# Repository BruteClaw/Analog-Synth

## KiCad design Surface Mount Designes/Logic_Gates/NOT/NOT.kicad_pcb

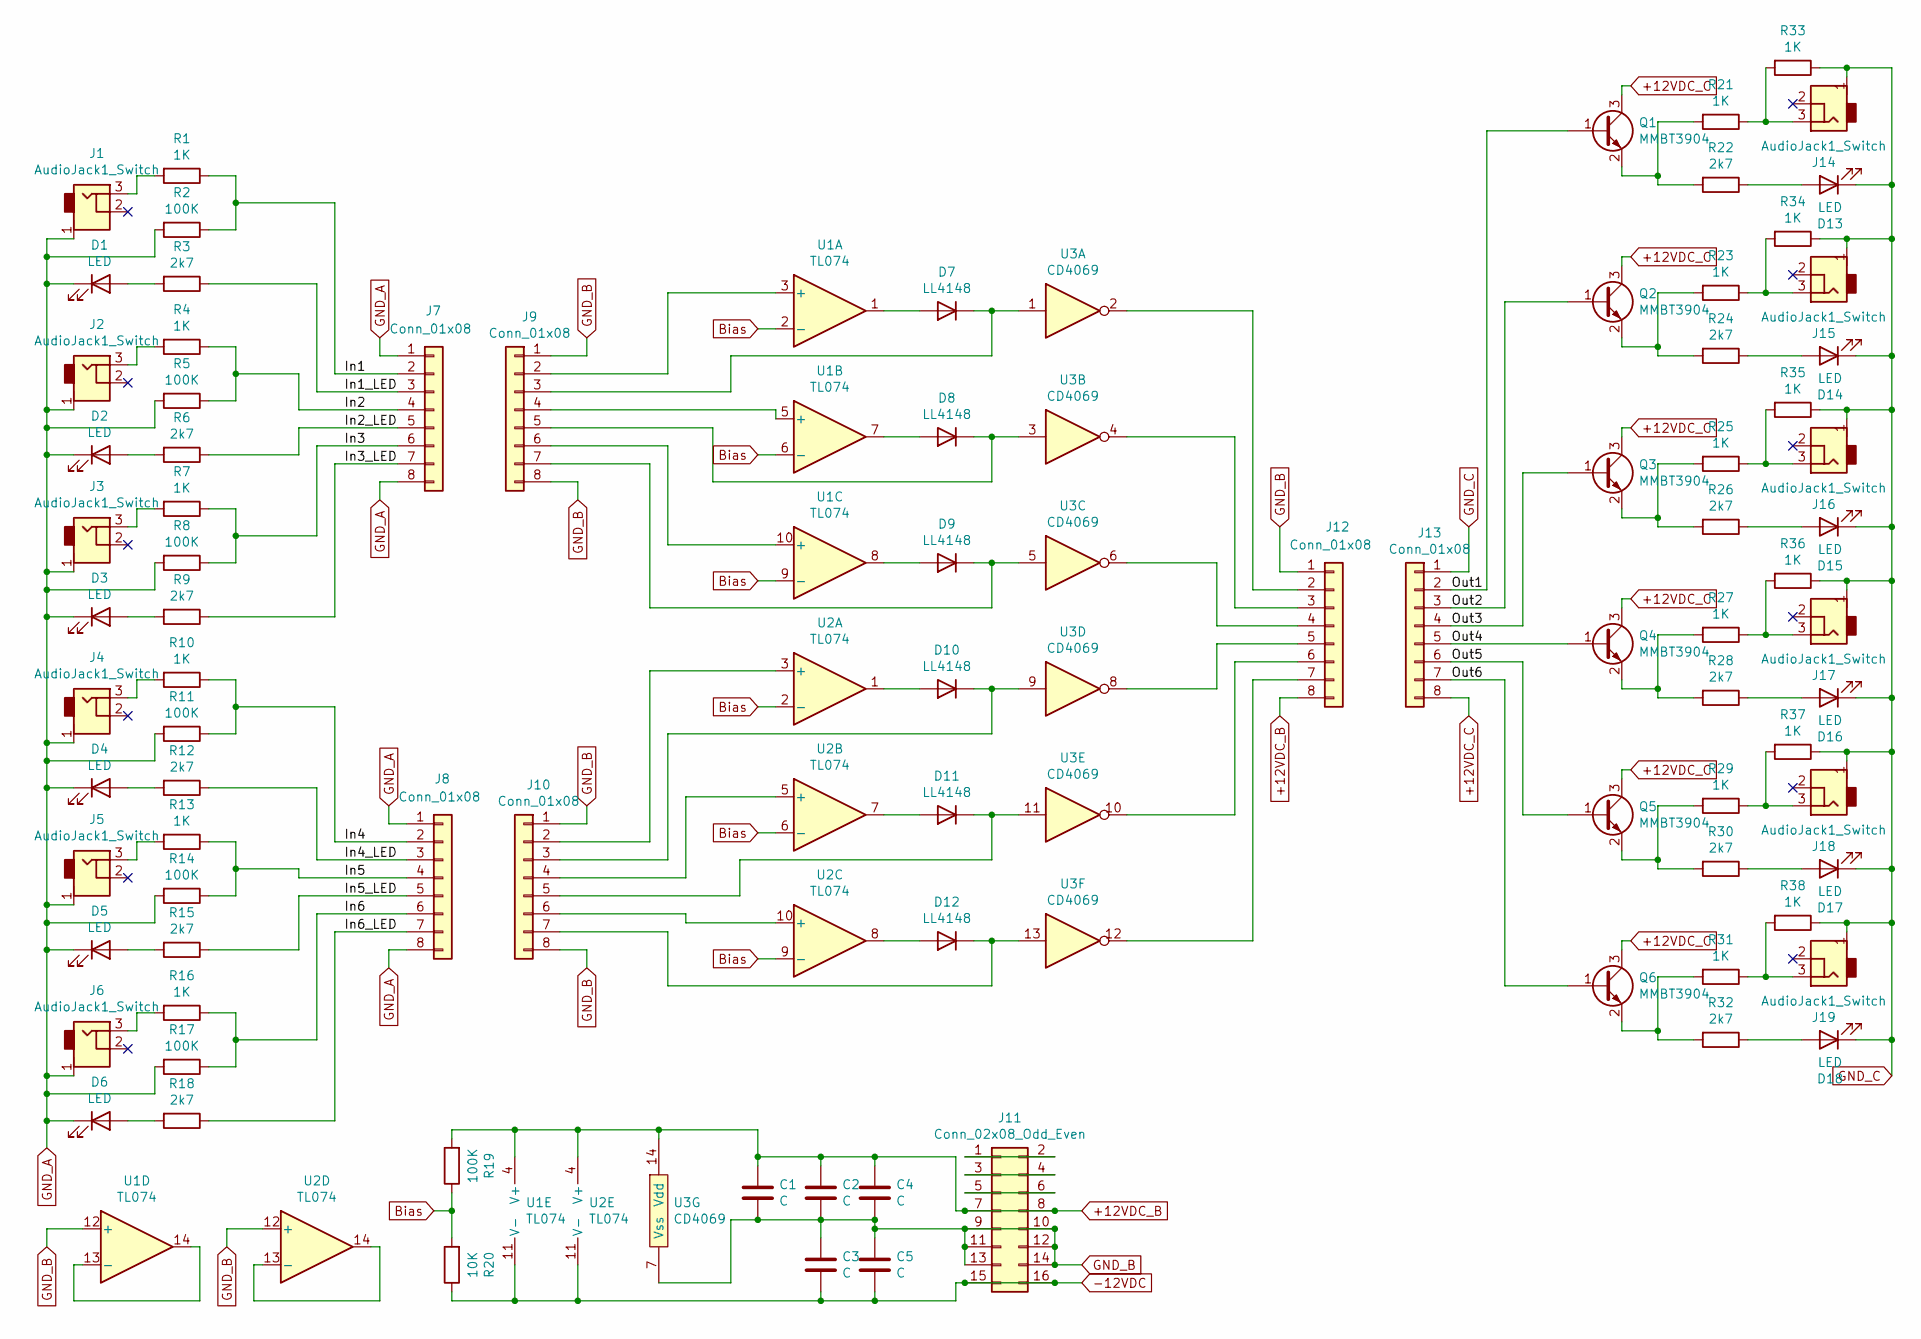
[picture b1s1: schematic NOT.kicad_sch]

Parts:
C1, C2, C3, C4, C5: C; C_1210_HandSoldering
D1, D2, D3, D4, D5, D6, D13, D14, D15, D16, D17, D18: LED; LED_Rectangular_W3.9mm_H1.9mm
D7, D8, D9, D10, D11, D12: LL4148; D_MiniMELF_Handsoldering
J1, J2, J3, J4, J5, J6, J14, J15, J16, J17, J18, J19: AudioJack1_Switch; Mono_Jack_3.5mm_Switch_Switchcraft_35RAPC2AH3
J7, J8, J9, J10, J12, J13: Conn_01x08; Pin_Header_Straight_1x08_Pitch2.54mm
J11: Conn_02x08_Odd_Even; Pin_Header_Straight_2x08_Pitch2.54mm
Q1, Q2, Q3, Q4, Q5, Q6: MMBT3904; SOT-23
R1, R4, R7, R10, R13, R16, R21, R23, R25, R27, R29, R31, R33, R34, R35, R36, R37, R38: 1K; R_1210_HandSoldering
R2, R5, R8, R11, R14, R17, R19: 100K; R_1210_HandSoldering
R3, R6, R9, R12, R15, R18, R22, R24, R26, R28, R30, R32: 2k7; R_1210_HandSoldering
R20: 10K; R_1210_HandSoldering
U1, U2: TL074; SOIC-14_3.9x8.7mm_Pitch1.27mm
U3: CD4069; SOIC-14_3.9x8.7mm_Pitch1.27mm

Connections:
+12VDC_B: C1.1, C2.1, C4.1, J11.7, J11.8, J12.8, R19.2, U1.4 (V+), U2.4 (V+), U3.14 (Vdd)
+12VDC_C: J13.8, Q1.3 (C), Q2.3 (C), Q3.3 (C), Q4.3 (C), Q5.3 (C), Q6.3 (C)
-12VDC: C3.2, C5.2, J11.15, J11.16, R20.1, U1.11 (V-), U2.11 (V-)
/In1: J7.2, R1.1, R2.1
/In1_LED: J7.3, R3.1
/In2: J7.4, R4.1, R5.1
/In2_LED: J7.5, R6.1
/In3: J7.6, R7.1, R8.1
/In3_LED: J7.7, R9.1
/In4: J8.2, R10.1, R11.1
/In4_LED: J8.3, R12.1
/In5: J8.4, R13.1, R14.1
/In5_LED: J8.5, R15.1
/In6: J8.6, R16.1, R17.1
/In6_LED: J8.7, R18.1
/Out1: J13.2, Q1.1 (B)
/Out2: J13.3, Q2.1 (B)
/Out3: J13.4, Q3.1 (B)
/Out4: J13.5, Q4.1 (B)
/Out5: J13.6, Q5.1 (B)
/Out6: J13.7, Q6.1 (B)
Bias: R19.1, R20.2, U1.2 (-), U1.6 (-), U1.9 (-), U2.2 (-), U2.6 (-), U2.9 (-)
GND_A: D1.1 (K), D2.1 (K), D3.1 (K), D4.1 (K), D5.1 (K), D6.1 (K), J1.1, J2.1, J3.1, J4.1, J5.1, J6.1, J7.1, J7.8, J8.1, J8.8, R2.2, R5.2, R8.2, R11.2, R14.2, R17.2
GND_B: C1.2, C2.2, C3.1, C4.2, C5.1, J9.1, J9.8, J10.1, J10.8, J11.9, J11.10, J11.11, J11.12, J11.13, J11.14, J12.1, U1.12 (+), U2.12 (+), U3.7 (Vss)
GND_C: D13.1 (K), D14.1 (K), D15.1 (K), D16.1 (K), D17.1 (K), D18.1 (K), J13.1, J14.1, J15.1, J16.1, J17.1, J18.1, J19.1, R33.1, R34.1, R35.1, R36.1, R37.1, R38.1
unnamed: D1.2 (A), R3.2
unnamed: D2.2 (A), R6.2
unnamed: D3.2 (A), R9.2
unnamed: D4.2 (A), R12.2
unnamed: D5.2 (A), R15.2
unnamed: D6.2 (A), R18.2
unnamed: D7.1 (K), J9.3, U3.1
unnamed: D7.2 (A), U1.1
unnamed: D8.1 (K), J9.5, U3.3
unnamed: D8.2 (A), U1.7
unnamed: D9.1 (K), J9.7, U3.5
unnamed: D9.2 (A), U1.8
unnamed: D10.1 (K), J10.3, U3.9
unnamed: D10.2 (A), U2.1
unnamed: D11.1 (K), J10.5, U3.11
unnamed: D11.2 (A), U2.7
unnamed: D12.1 (K), J10.7, U3.13
unnamed: D12.2 (A), U2.8
unnamed: D13.2 (A), R22.1
unnamed: D14.2 (A), R24.1
unnamed: D15.2 (A), R26.1
unnamed: D16.2 (A), R28.1
unnamed: D17.2 (A), R30.1
unnamed: D18.2 (A), R32.1
unnamed: J1.3, R1.2
unnamed: J2.3, R4.2
unnamed: J3.3, R7.2
unnamed: J4.3, R10.2
unnamed: J5.3, R13.2
unnamed: J6.3, R16.2
unnamed: J9.2, U1.3 (+)
unnamed: J9.4, U1.5 (+)
unnamed: J9.6, U1.10 (+)
unnamed: J10.2, U2.3 (+)
unnamed: J10.4, U2.5 (+)
unnamed: J10.6, U2.10 (+)
unnamed: J11.1, J11.2
unnamed: J11.3, J11.4
unnamed: J11.5, J11.6
unnamed: J12.2, U3.2
unnamed: J12.3, U3.4
unnamed: J12.4, U3.6
unnamed: J12.5, U3.8
unnamed: J12.6, U3.10
unnamed: J12.7, U3.12
unnamed: J14.3, R21.1, R33.2
unnamed: J15.3, R23.1, R34.2
unnamed: J16.3, R25.1, R35.2
unnamed: J17.3, R27.1, R36.2
unnamed: J18.3, R29.1, R37.2
unnamed: J19.3, R31.1, R38.2
unnamed: Q1.2 (E), R21.2, R22.2
unnamed: Q2.2 (E), R23.2, R24.2
unnamed: Q3.2 (E), R25.2, R26.2
unnamed: Q4.2 (E), R27.2, R28.2
unnamed: Q5.2 (E), R29.2, R30.2
unnamed: Q6.2 (E), R31.2, R32.2
unnamed: U1.13 (-), U1.14
unnamed: U2.13 (-), U2.14

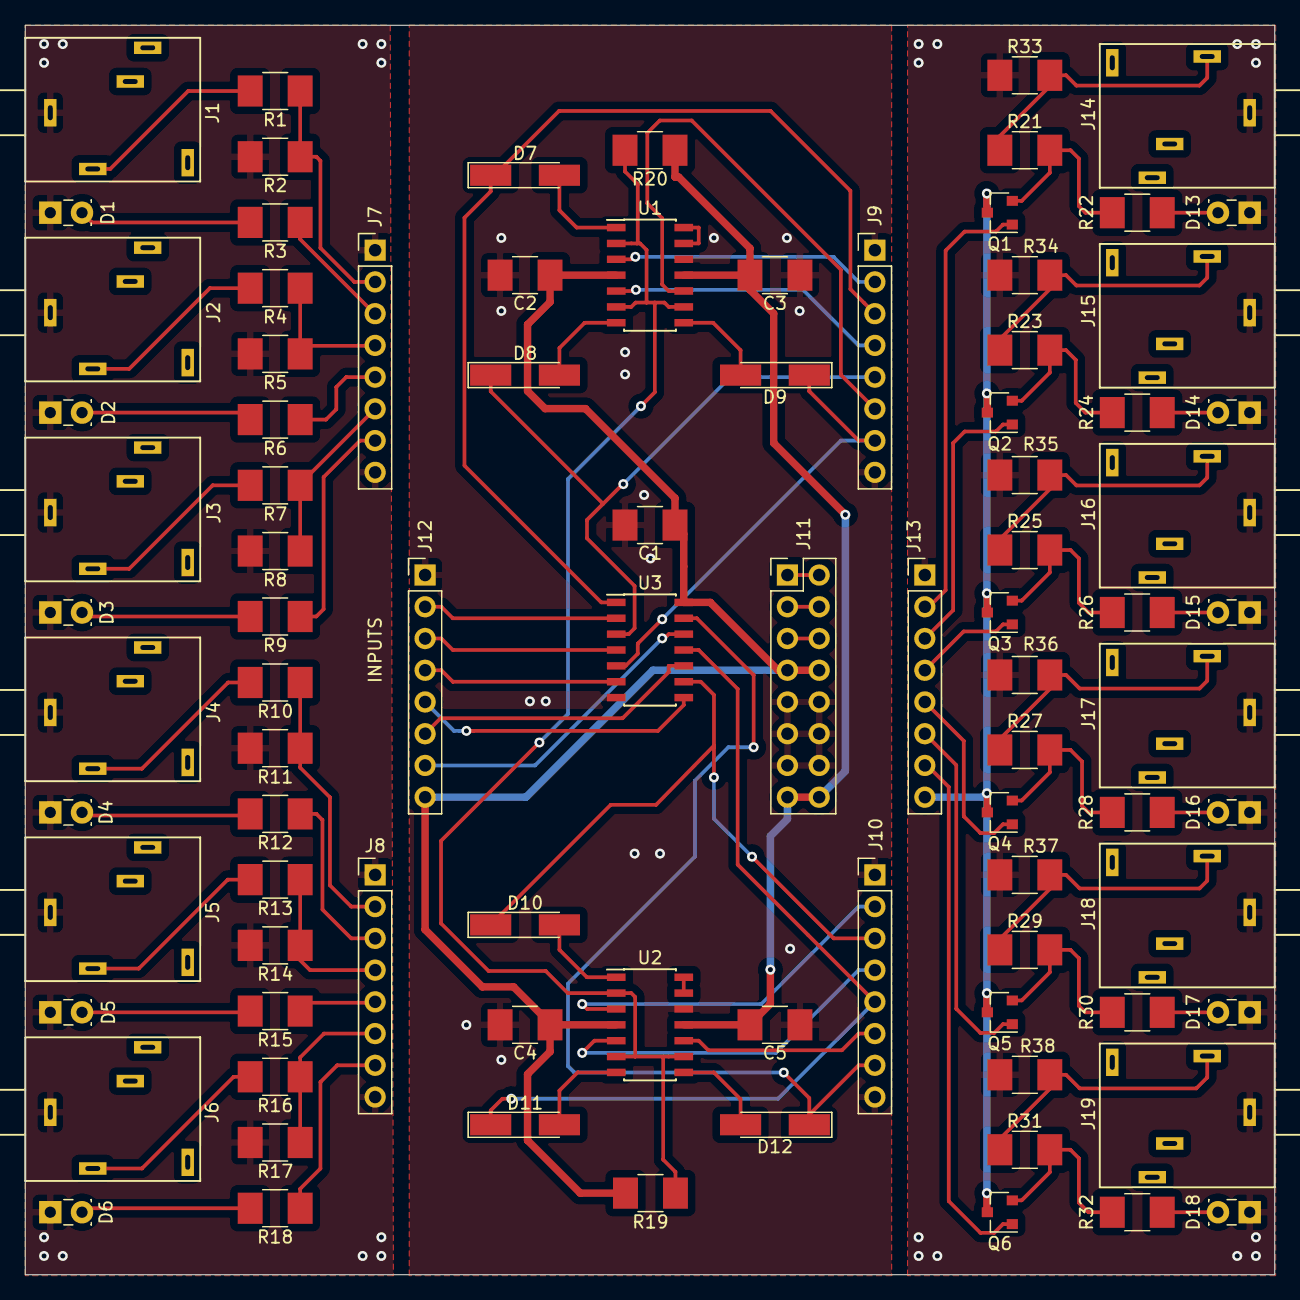
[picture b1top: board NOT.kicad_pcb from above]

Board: 2 copper layers, 100.0 x 100.0 mm, 89 parts (0 on the bottom side), 84 nets.

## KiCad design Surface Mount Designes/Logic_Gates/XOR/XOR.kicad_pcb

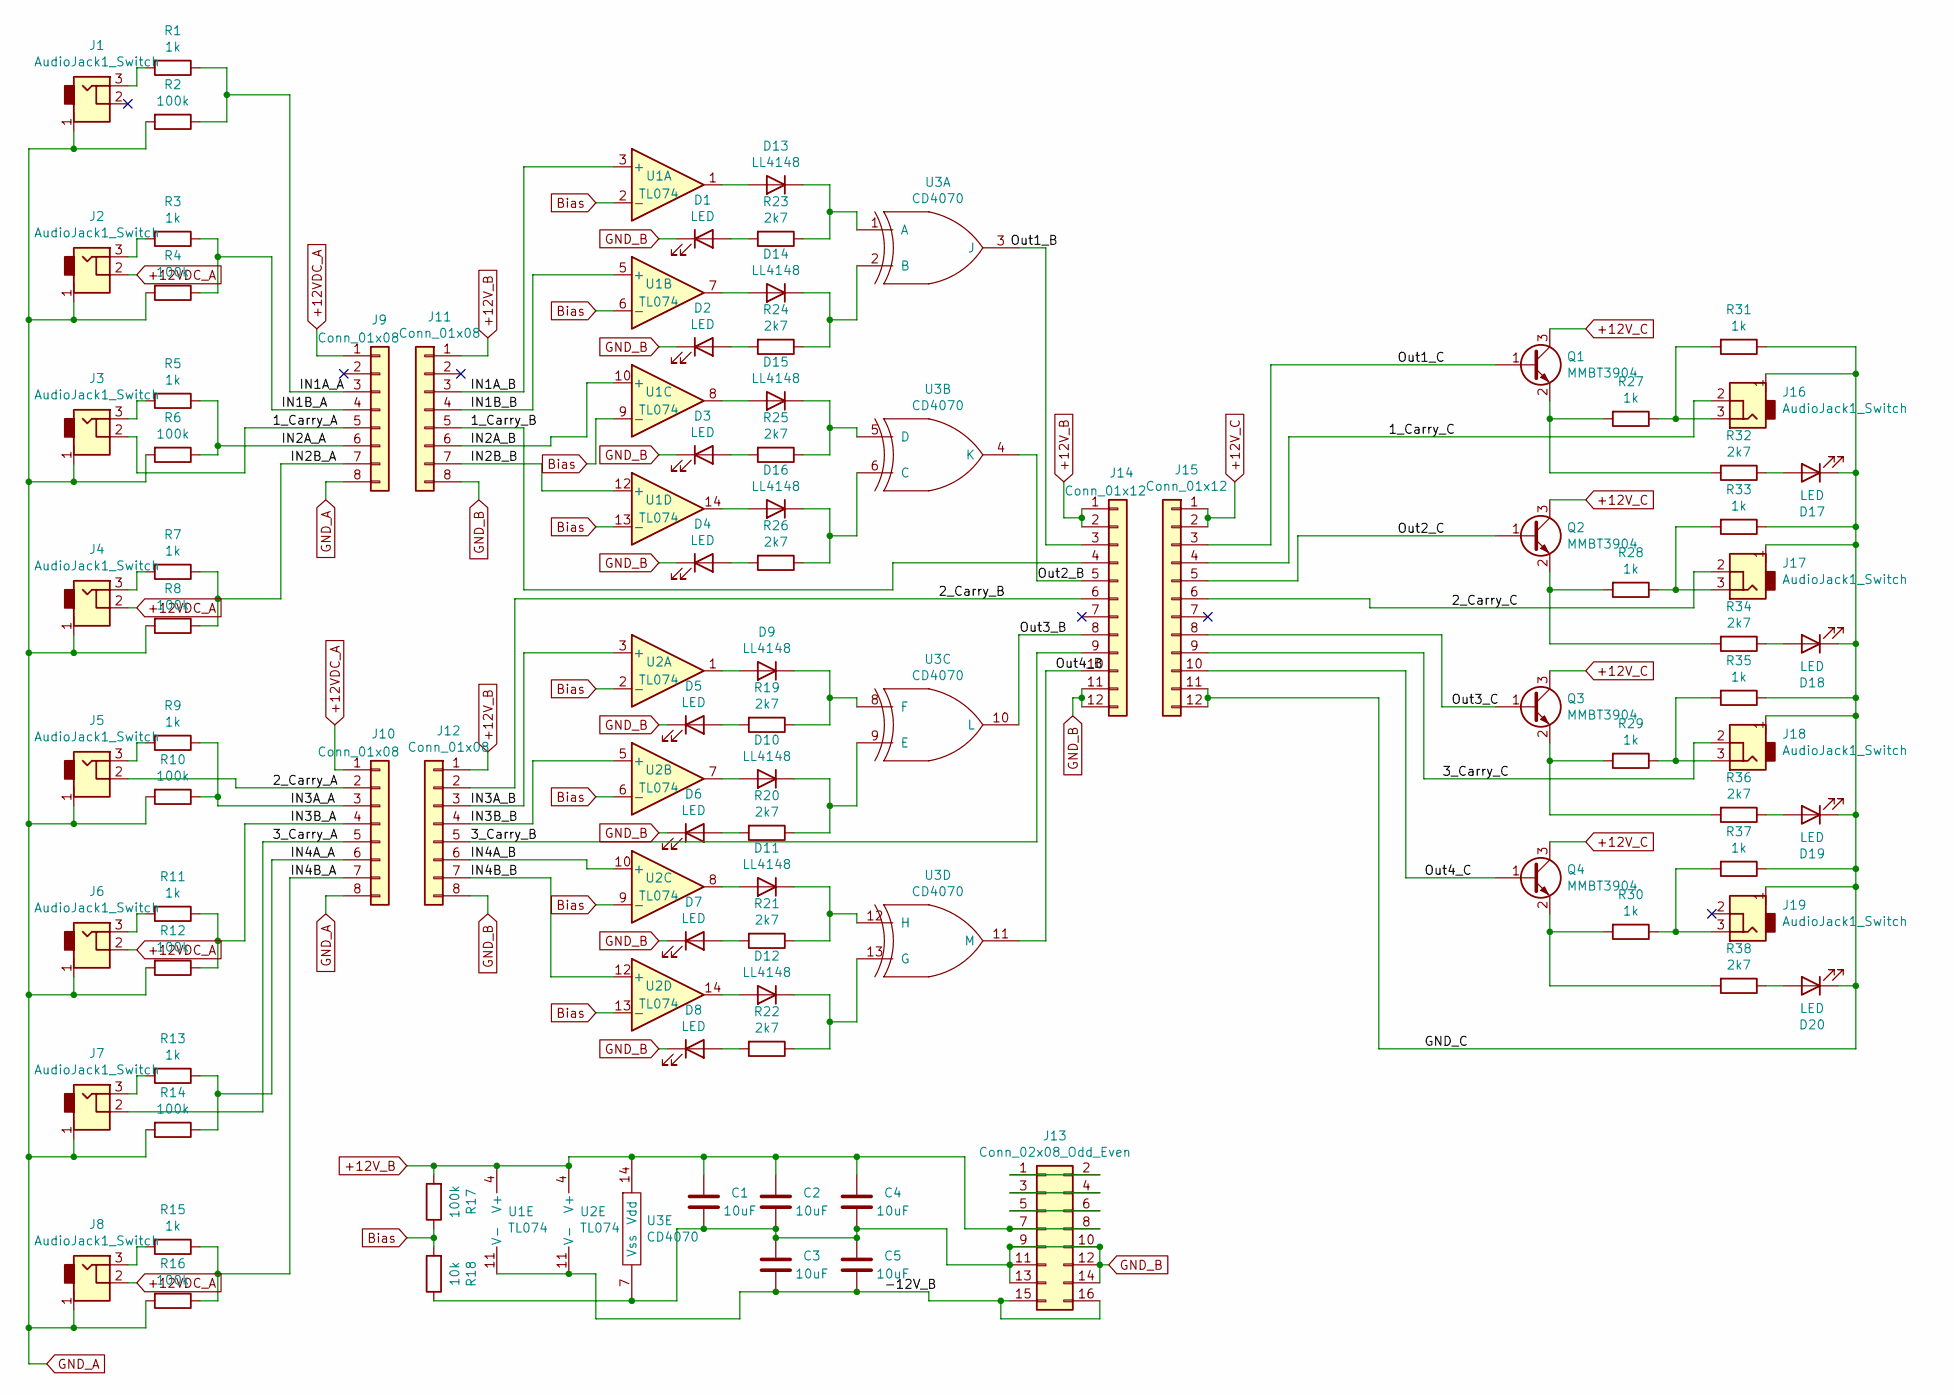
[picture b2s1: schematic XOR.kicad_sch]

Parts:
C1, C2, C3, C4, C5: 10uF; C_1210_HandSoldering
D1, D2, D3, D4, D5, D6, D7, D8, D17, D18, D19, D20: LED; LED_Rectangular_W3.9mm_H1.9mm
D9, D10, D11, D12, D13, D14, D15, D16: LL4148; D_MiniMELF_Handsoldering
J1, J2, J3, J4, J5, J6, J7, J8, J16, J17, J18, J19: AudioJack1_Switch; Mono_Jack_3.5mm_Switch_Switchcraft_35RAPC2AH3
J9, J10, J11, J12: Conn_01x08; Pin_Header_Straight_1x08_Pitch2.54mm
J13: Conn_02x08_Odd_Even; Pin_Header_Straight_2x08_Pitch2.54mm
J14, J15: Conn_01x12; Pin_Header_Straight_1x12_Pitch2.54mm
Q1, Q2, Q3, Q4: MMBT3904; SOT-23
R1, R3, R5, R7, R9, R11, R13, R15, R27, R28, R29, R30, R31, R33, R35, R37: 1k; R_1210_HandSoldering
R2, R4, R6, R8, R10, R12, R14, R16, R17: 100k; R_1210_HandSoldering
R18: 10k; R_1210_HandSoldering
R19, R20, R21, R22, R23, R24, R25, R26, R32, R34, R36, R38: 2k7; R_1210_HandSoldering
U1, U2: TL074; SOIC-14_3.9x8.7mm_Pitch1.27mm
U3: CD4070; SOIC-14_3.9x8.7mm_Pitch1.27mm

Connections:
+12VDC_A: J2.2, J4.2, J6.2, J8.2, J9.1, J10.1
+12V_B: C1.2, C2.2, C4.2, J11.1, J12.1, J13.7, J13.8, J14.1, J14.2, R17.2, U1.4 (V+), U2.4 (V+), U3.14 (Vdd)
+12V_C: J15.1, J15.2, Q1.3 (C), Q2.3 (C), Q3.3 (C), Q4.3 (C)
/1_Carry_A: J3.2, J9.5
/1_Carry_B: J11.5, J14.4
/1_Carry_C: J15.4, J16.2
/2_Carry_A: J5.2, J10.2
/2_Carry_B: J12.2, J14.6
/2_Carry_C: J15.6, J17.2
/3_Carry_A: J7.2, J10.5
/3_Carry_B: J12.5, J14.9
/3_Carry_C: J15.9, J18.2
/-12V_B: C3.1, C5.1, J13.15, J13.16, U1.11 (V-), U2.11 (V-)
/GND_C: D17.1 (K), D18.1 (K), D19.1 (K), D20.1 (K), J15.11, J15.12, J16.1, J17.1, J18.1, J19.1, R31.1, R33.1, R35.1, R37.1
/IN1A_A: J9.3, R1.1, R2.1
/IN1A_B: J11.3, U1.3 (+)
/IN1B_A: J9.4, R3.1, R4.1
/IN1B_B: J11.4, U1.5 (+)
/IN2A_A: J9.6, R5.1, R6.1
/IN2A_B: J11.6, U1.10 (+)
/IN2B_A: J9.7, R7.1, R8.1
/IN2B_B: J11.7, U1.12 (+)
/IN3A_A: J10.3, R9.1, R10.1
/IN3A_B: J12.3, U2.3 (+)
/IN3B_A: J10.4, R11.1, R12.1
/IN3B_B: J12.4, U2.5 (+)
/IN4A_A: J10.6, R13.1, R14.1
/IN4A_B: J12.6, U2.10 (+)
/IN4B_A: J10.7, R15.1, R16.1
/IN4B_B: J12.7, U2.12 (+)
/Out1_C: J15.3, Q1.1 (B)
/Out2_B: J14.5, U3.4 (K)
/Out2_C: J15.5, Q2.1 (B)
/Out3_B: J14.8, U3.10 (L)
/Out3_C: J15.8, Q3.1 (B)
/Out4_B: J14.10, U3.11 (M)
/Out4_C: J15.10, Q4.1 (B)
Bias: R17.1, R18.2, U1.2 (-), U1.6 (-), U1.9 (-), U1.13 (-), U2.2 (-), U2.6 (-), U2.9 (-), U2.13 (-)
GND_A: J1.1, J2.1, J3.1, J4.1, J5.1, J6.1, J7.1, J8.1, J9.8, J10.8, R2.2, R4.2, R6.2, R8.2, R10.2, R12.2, R14.2, R16.2
GND_B: C1.1, C2.1, C3.2, C4.1, C5.2, D1.1 (K), D2.1 (K), D3.1 (K), D4.1 (K), D5.1 (K), D6.1 (K), D7.1 (K), D8.1 (K), J11.8, J12.8, J13.9, J13.10, J13.11, J13.12, J13.13, J13.14, J14.11, J14.12, R18.1, U3.7 (Vss)
unnamed: D1.2 (A), R23.2
unnamed: D2.2 (A), R24.2
unnamed: D3.2 (A), R25.2
unnamed: D4.2 (A), R26.2
unnamed: D5.2 (A), R19.2
unnamed: D6.2 (A), R20.2
unnamed: D7.2 (A), R21.2
unnamed: D8.2 (A), R22.2
unnamed: D9.1 (K), R19.1, U3.8 (F)
unnamed: D9.2 (A), U2.1
unnamed: D10.1 (K), R20.1, U3.9 (E)
unnamed: D10.2 (A), U2.7
unnamed: D11.1 (K), R21.1, U3.12 (H)
unnamed: D11.2 (A), U2.8
unnamed: D12.1 (K), R22.1, U3.13 (G)
unnamed: D12.2 (A), U2.14
unnamed: D13.1 (K), R23.1, U3.1 (A)
unnamed: D13.2 (A), U1.1
unnamed: D14.1 (K), R24.1, U3.2 (B)
unnamed: D14.2 (A), U1.7
unnamed: D15.1 (K), R25.1, U3.5 (D)
unnamed: D15.2 (A), U1.8
unnamed: D16.1 (K), R26.1, U3.6 (C)
unnamed: D16.2 (A), U1.14
unnamed: D17.2 (A), R32.1
unnamed: D18.2 (A), R34.1
unnamed: D19.2 (A), R36.1
unnamed: D20.2 (A), R38.1
unnamed: J1.3, R1.2
unnamed: J2.3, R3.2
unnamed: J3.3, R5.2
unnamed: J4.3, R7.2
unnamed: J5.3, R9.2
unnamed: J6.3, R11.2
unnamed: J7.3, R13.2
unnamed: J8.3, R15.2
unnamed: J13.1, J13.2
unnamed: J13.3, J13.4
unnamed: J13.5, J13.6
unnamed: J14.3, U3.3 (J)
unnamed: J16.3, R27.1, R31.2
unnamed: J17.3, R28.1, R33.2
unnamed: J18.3, R29.1, R35.2
unnamed: J19.3, R30.1, R37.2
unnamed: Q1.2 (E), R27.2, R32.2
unnamed: Q2.2 (E), R28.2, R34.2
unnamed: Q3.2 (E), R29.2, R36.2
unnamed: Q4.2 (E), R30.2, R38.2

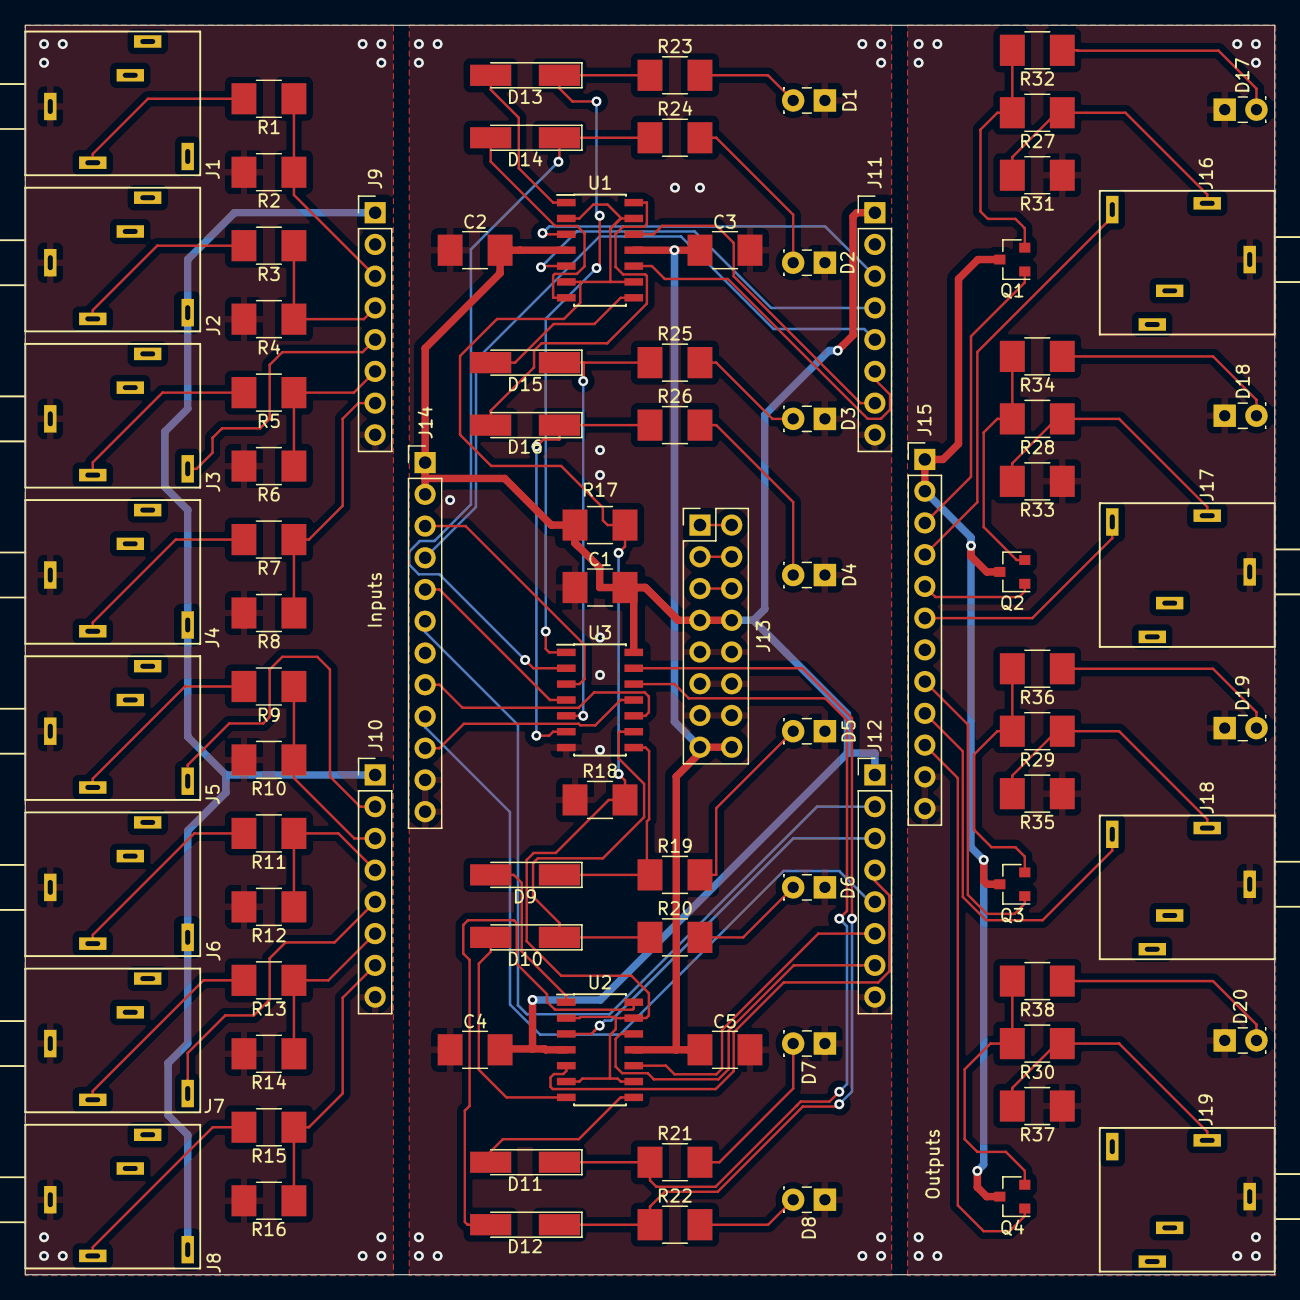
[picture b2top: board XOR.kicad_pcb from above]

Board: 2 copper layers, 100.0 x 100.0 mm, 89 parts (0 on the bottom side), 88 nets.

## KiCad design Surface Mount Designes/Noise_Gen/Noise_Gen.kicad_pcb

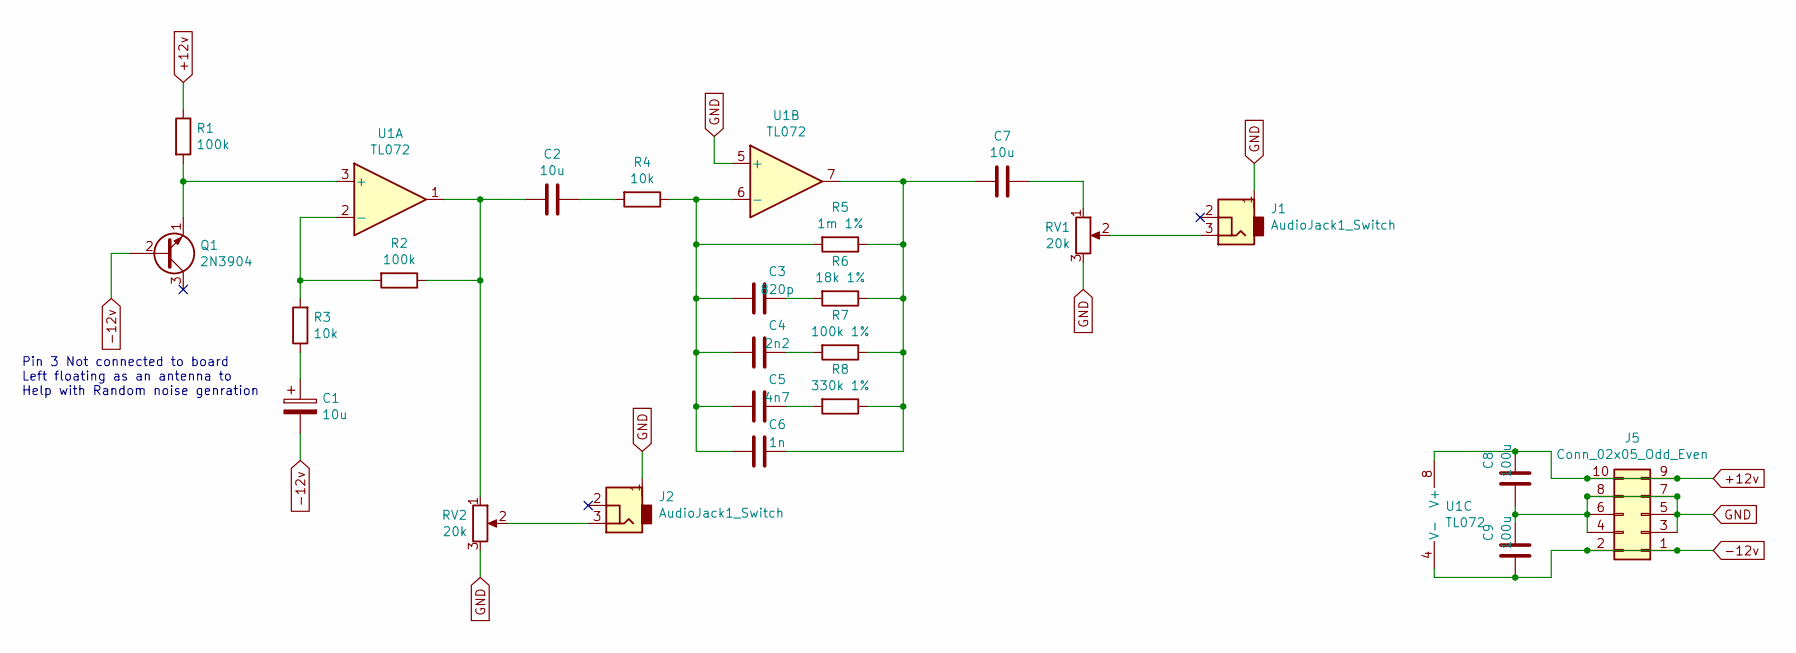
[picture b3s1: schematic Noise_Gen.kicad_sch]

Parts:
C1: 10u; CP_Elec_4x4.5
C2, C7: 10u; C_1210_HandSoldering
C3: 820p; C_1210_HandSoldering
C4: 2n2; C_1210_HandSoldering
C5: 4n7; C_1210_HandSoldering
C6: 1n; C_1210_HandSoldering
C8, C9: 100u; CP_Elec_6.3x7.7
J1, J2: AudioJack1_Switch; Mono_Jack_3.5mm_Switch_Switchcraft_35RAPC2AH3
J5: Conn_02x05_Odd_Even; Pin_Header_Straight_2x05_Pitch2.54mm
Q1: 2N3904; TO-92_Inline_Wide
R1, R2: 100k; R_1210_HandSoldering
R3, R4: 10k; R_1210_HandSoldering
R5: 1m 1%; R_1210_HandSoldering
R6: 18k 1%; R_1210_HandSoldering
R7: 100k 1%; R_1210_HandSoldering
R8: 330k 1%; R_1210_HandSoldering
RV1, RV2: 20k; Potentiometer_Bourns_PTV09A-2_Vertical
U1: TL072; SOIC-8_3.9x4.9mm_Pitch1.27mm

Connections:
+12v: C8.1, J5.9, J5.10, R1.1, U1.8 (V+)
-12v: C1.2, C9.2, J5.1, J5.2, Q1.2 (B), U1.4 (V-)
GND: C8.2, C9.1, J1.1, J2.1, J5.3, J5.4, J5.5, J5.6, J5.7, J5.8, RV1.3, RV2.3, U1.5 (+)
unnamed: C1.1, R3.1
unnamed: C2.1, R4.2
unnamed: C2.2, R2.1, RV2.1, U1.1
unnamed: C3.1, R6.2
unnamed: C3.2, C4.2, C5.2, C6.2, R4.1, R5.2, U1.6 (-)
unnamed: C4.1, R7.2
unnamed: C5.1, R8.2
unnamed: C6.1, C7.2, R5.1, R6.1, R7.1, R8.1, U1.7
unnamed: C7.1, RV1.1
unnamed: J1.3, RV1.2
unnamed: J2.3, RV2.2
unnamed: Q1.1 (E), R1.2, U1.3 (+)
unnamed: R2.2, R3.2, U1.2 (-)

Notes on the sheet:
Pin 3 Not connected to board Left floating as an antenna to Help with Random noise genration

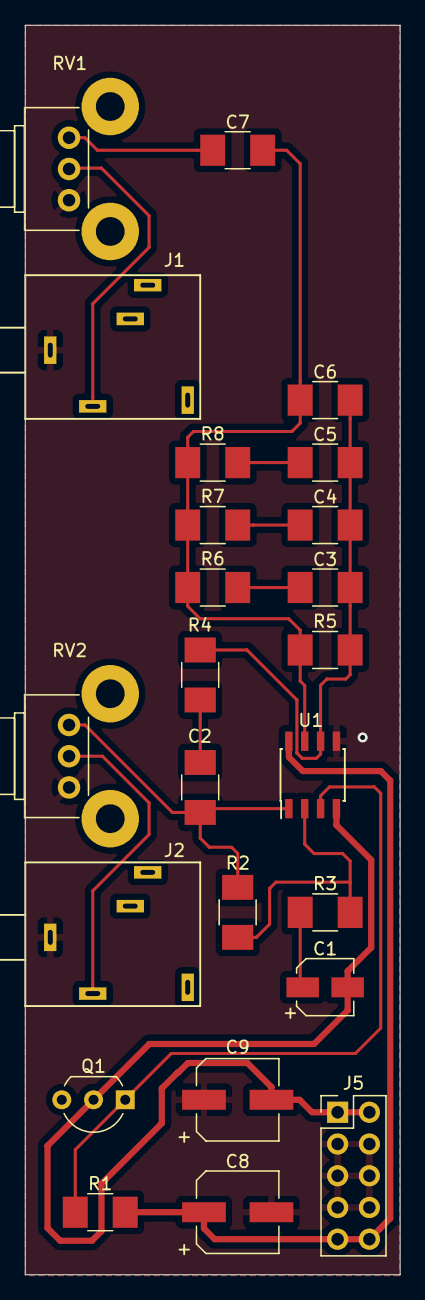
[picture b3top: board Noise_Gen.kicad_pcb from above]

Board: 2 copper layers, 30.0 x 100.0 mm, 24 parts (0 on the bottom side), 16 nets.

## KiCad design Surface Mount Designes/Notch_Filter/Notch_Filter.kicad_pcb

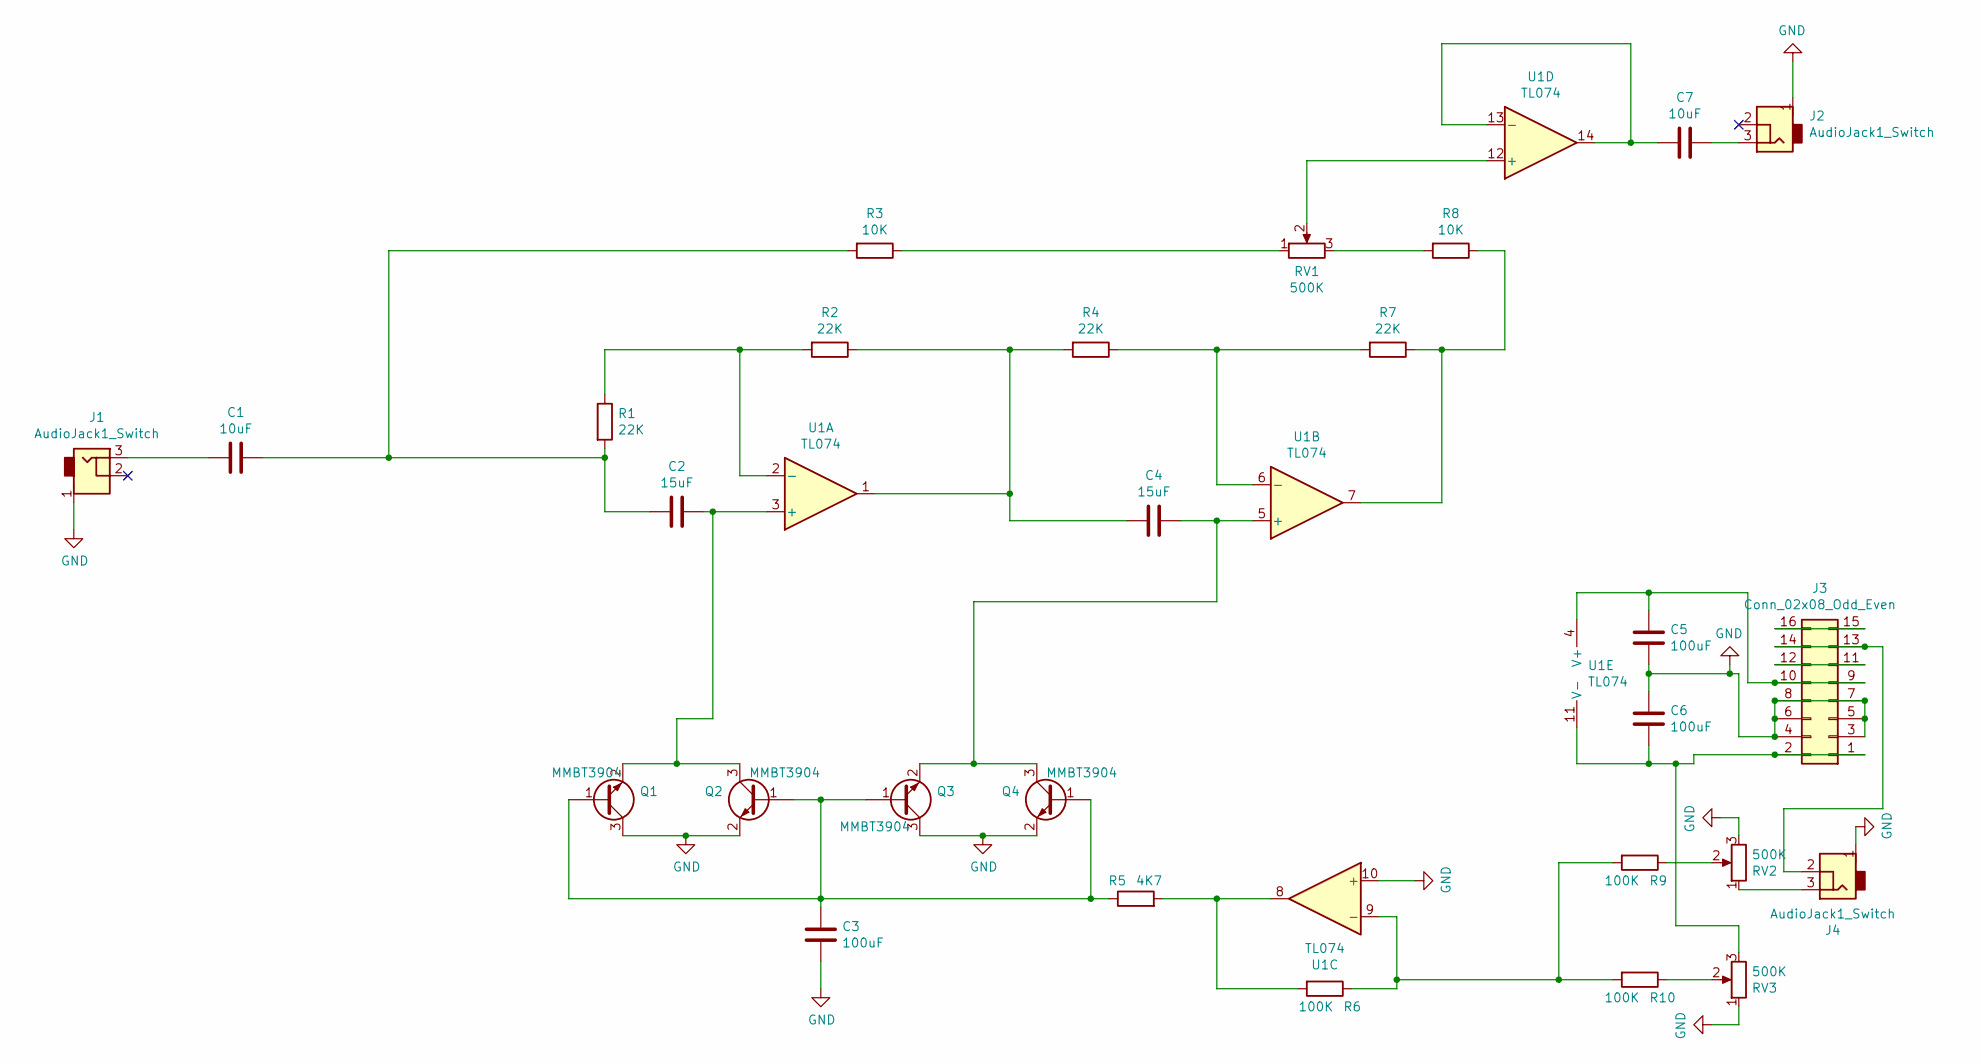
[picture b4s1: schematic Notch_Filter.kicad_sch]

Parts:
C1, C7: 10uF; C_1210_HandSoldering
C2, C4: 15uF; C_1210_HandSoldering
C3, C5, C6: 100uF; C_1210_HandSoldering
J1, J2, J4: AudioJack1_Switch; Mono_Jack_3.5mm_Switch_Switchcraft_35RAPC2AH3
J3: Conn_02x08_Odd_Even; Pin_Header_Straight_2x08_Pitch2.54mm
Q1, Q2, Q3, Q4: MMBT3904; SOT-23
R1, R2, R4, R7: 22K; R_1210_HandSoldering
R3, R8: 10K; R_1210_HandSoldering
R5: 4K7; R_1210_HandSoldering
R6, R9, R10: 100K; R_1210_HandSoldering
RV1, RV2, RV3: 500K; Potentiometer_Bourns_PTV09A-2_Vertical
U1: TL074; SOIC-14_N

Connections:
GND: C3.2, C5.2, C6.1, J1.1, J2.1, J3.3, J3.4, J3.5, J3.6, J3.7, J3.8, J4.1, Q1.3 (C), Q2.2 (E), Q3.3 (C), Q4.2 (E), RV2.3, RV3.1, U1.10 (+)
unnamed: C1.1, C2.2, R1.2, R3.2
unnamed: C1.2, J1.3
unnamed: C2.1, Q1.2 (E), Q2.3 (C), U1.3 (+)
unnamed: C3.1, Q1.1 (B), Q2.1 (B), Q3.1 (B), Q4.1 (B), R5.1
unnamed: C4.1, Q3.2 (E), Q4.3 (C), U1.5 (+)
unnamed: C4.2, R2.1, R4.2, U1.1
unnamed: C5.1, J3.9, J3.10, U1.4 (V+)
unnamed: C6.2, J3.1, J3.2, RV3.3, U1.11 (V-)
unnamed: C7.1, J2.3
unnamed: C7.2, U1.13 (-), U1.14
unnamed: J3.11, J3.12
unnamed: J3.13, J3.14, J4.2
unnamed: J3.15, J3.16
unnamed: J4.3, RV2.1
unnamed: R1.1, R2.2, U1.2 (-)
unnamed: R3.1, RV1.1
unnamed: R4.1, R7.2, U1.6 (-)
unnamed: R5.2, R6.2, U1.8
unnamed: R7.1, R8.1, U1.7
unnamed: R8.2, RV1.3
unnamed: R9.1, RV2.2
unnamed: R10.1, RV3.2
unnamed: R6.1, R9.2, R10.2, U1.9 (-)
unnamed: RV1.2, U1.12 (+)

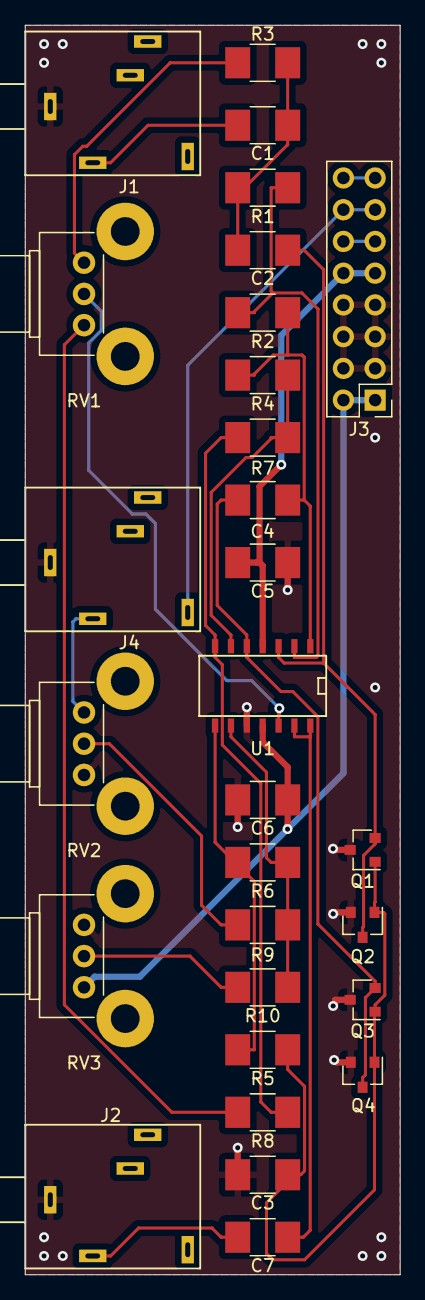
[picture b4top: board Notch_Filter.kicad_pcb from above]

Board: 2 copper layers, 30.0 x 100.0 mm, 29 parts (0 on the bottom side), 25 nets.

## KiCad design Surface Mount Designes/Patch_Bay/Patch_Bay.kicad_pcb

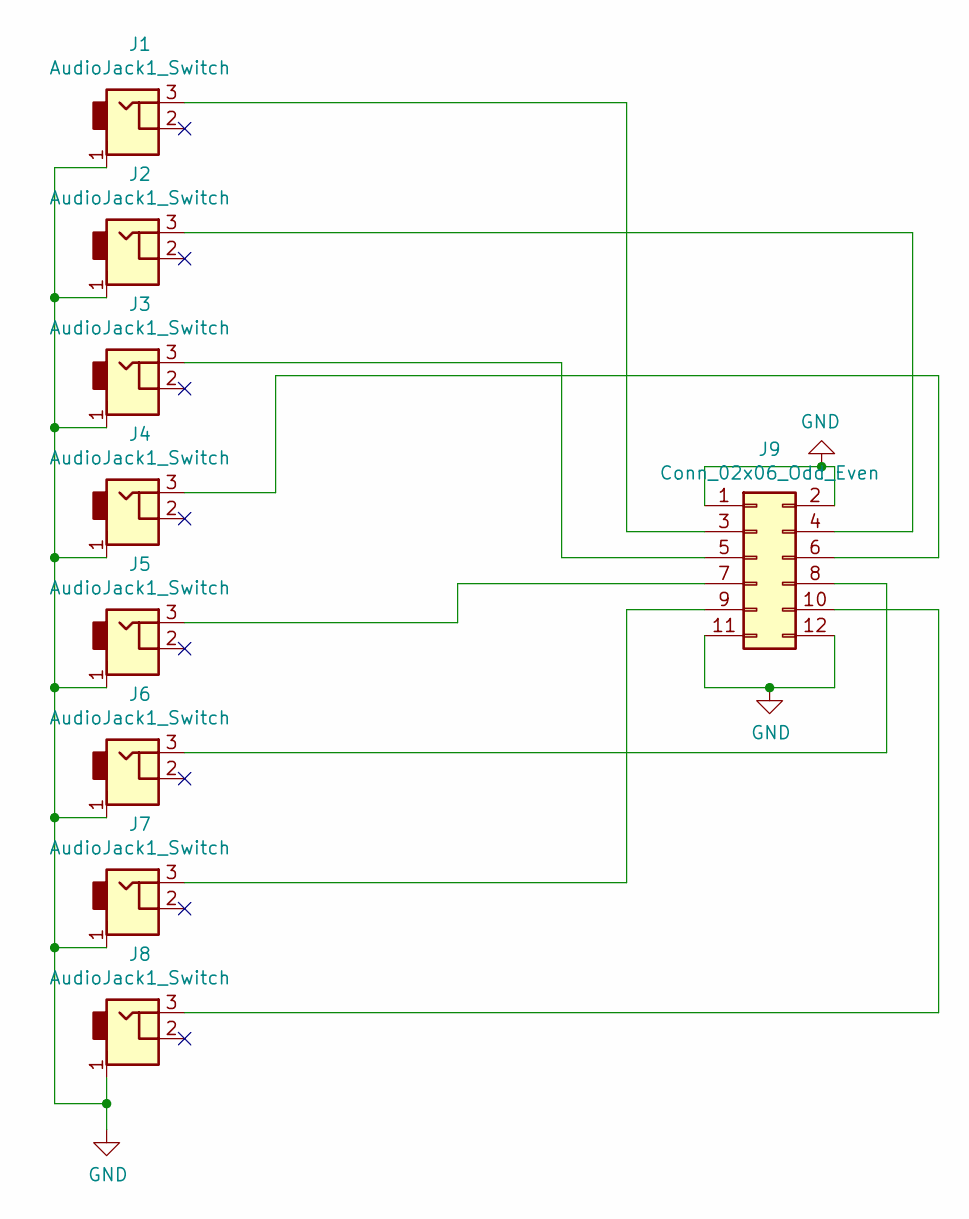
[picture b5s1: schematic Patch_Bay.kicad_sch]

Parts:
J1, J2, J3, J4, J5, J6, J7, J8: AudioJack1_Switch; Mono_Jack_3.5mm_Switch_Switchcraft_35RAPC2AH3
J9: Conn_02x06_Odd_Even; Pin_Header_Straight_2x06_Pitch2.54mm

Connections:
GND: J1.1, J2.1, J3.1, J4.1, J5.1, J6.1, J7.1, J8.1, J9.1, J9.2, J9.11, J9.12
unnamed: J1.3, J9.3
unnamed: J2.3, J9.4
unnamed: J3.3, J9.5
unnamed: J4.3, J9.6
unnamed: J5.3, J9.7
unnamed: J6.3, J9.8
unnamed: J7.3, J9.9
unnamed: J8.3, J9.10

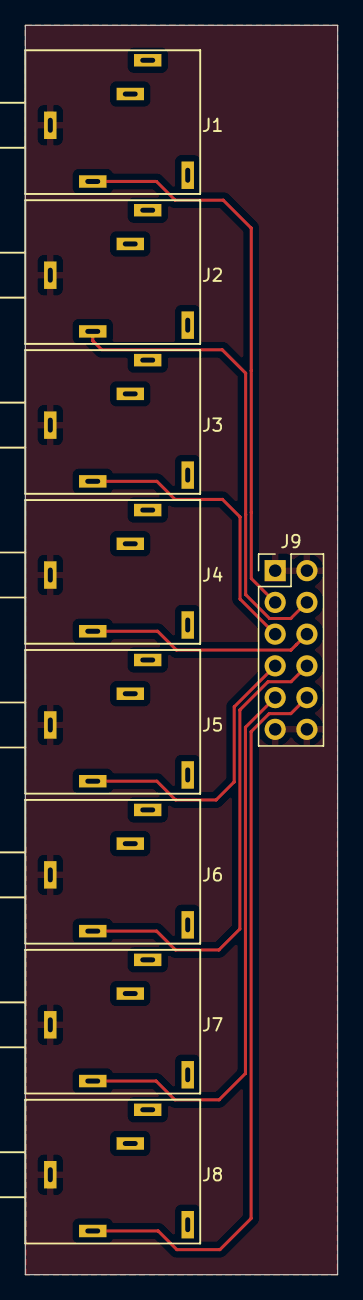
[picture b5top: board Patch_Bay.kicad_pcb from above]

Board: 2 copper layers, 25.0 x 100.0 mm, 9 parts (0 on the bottom side), 9 nets.
